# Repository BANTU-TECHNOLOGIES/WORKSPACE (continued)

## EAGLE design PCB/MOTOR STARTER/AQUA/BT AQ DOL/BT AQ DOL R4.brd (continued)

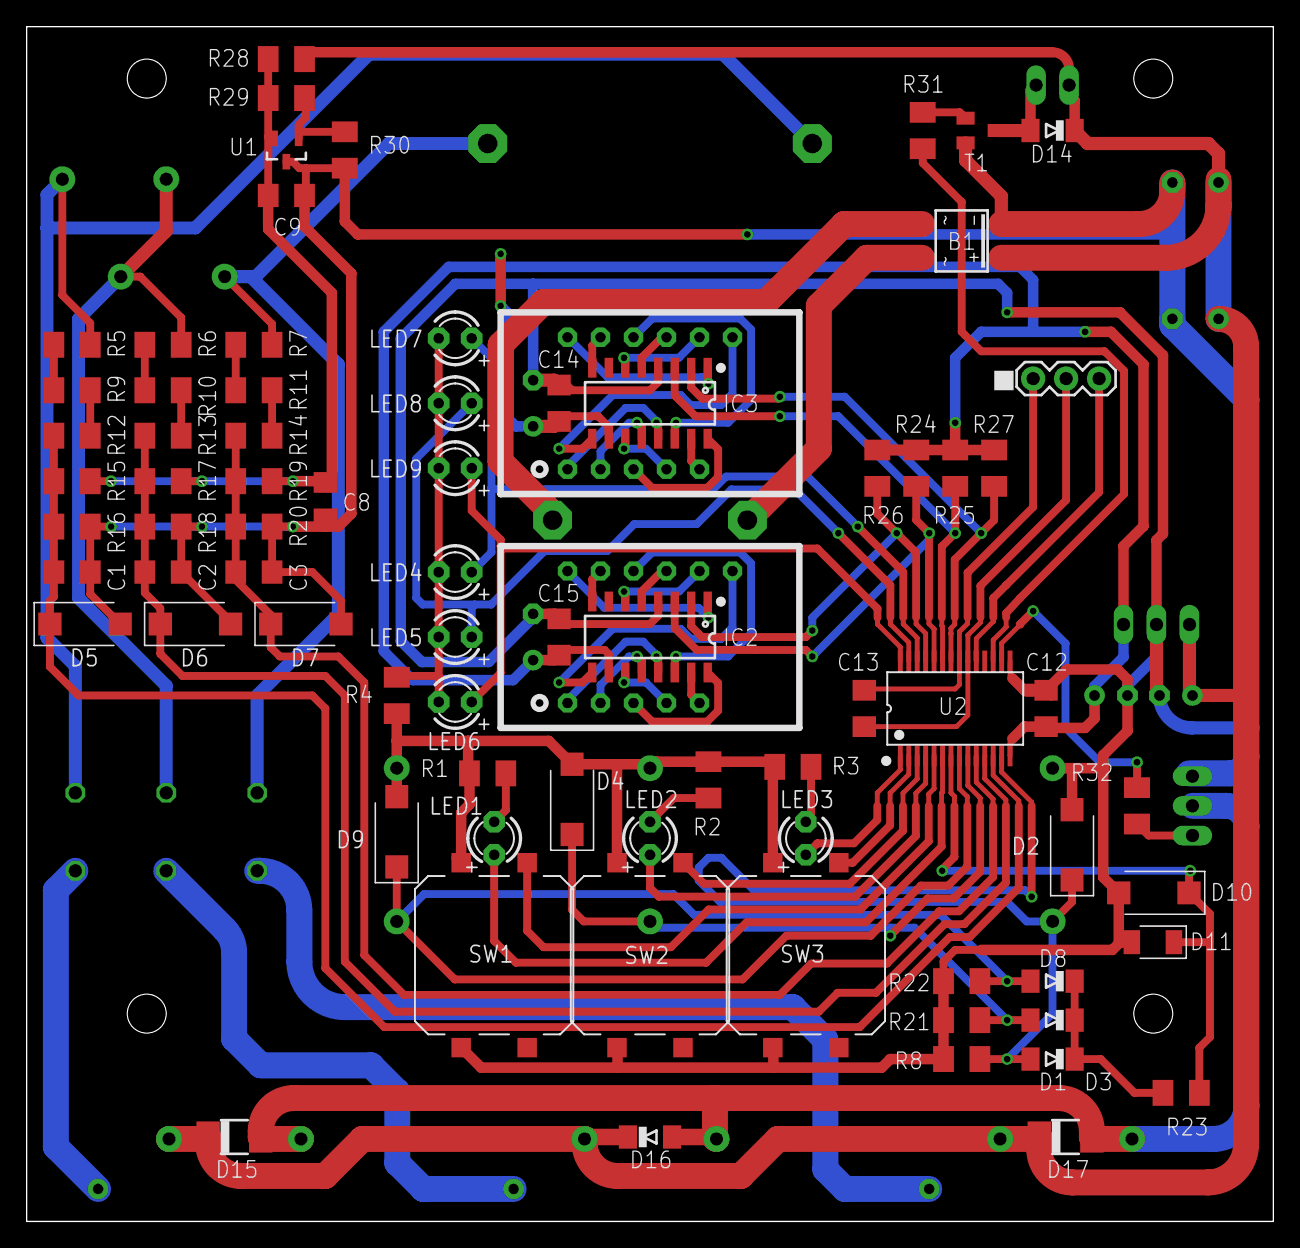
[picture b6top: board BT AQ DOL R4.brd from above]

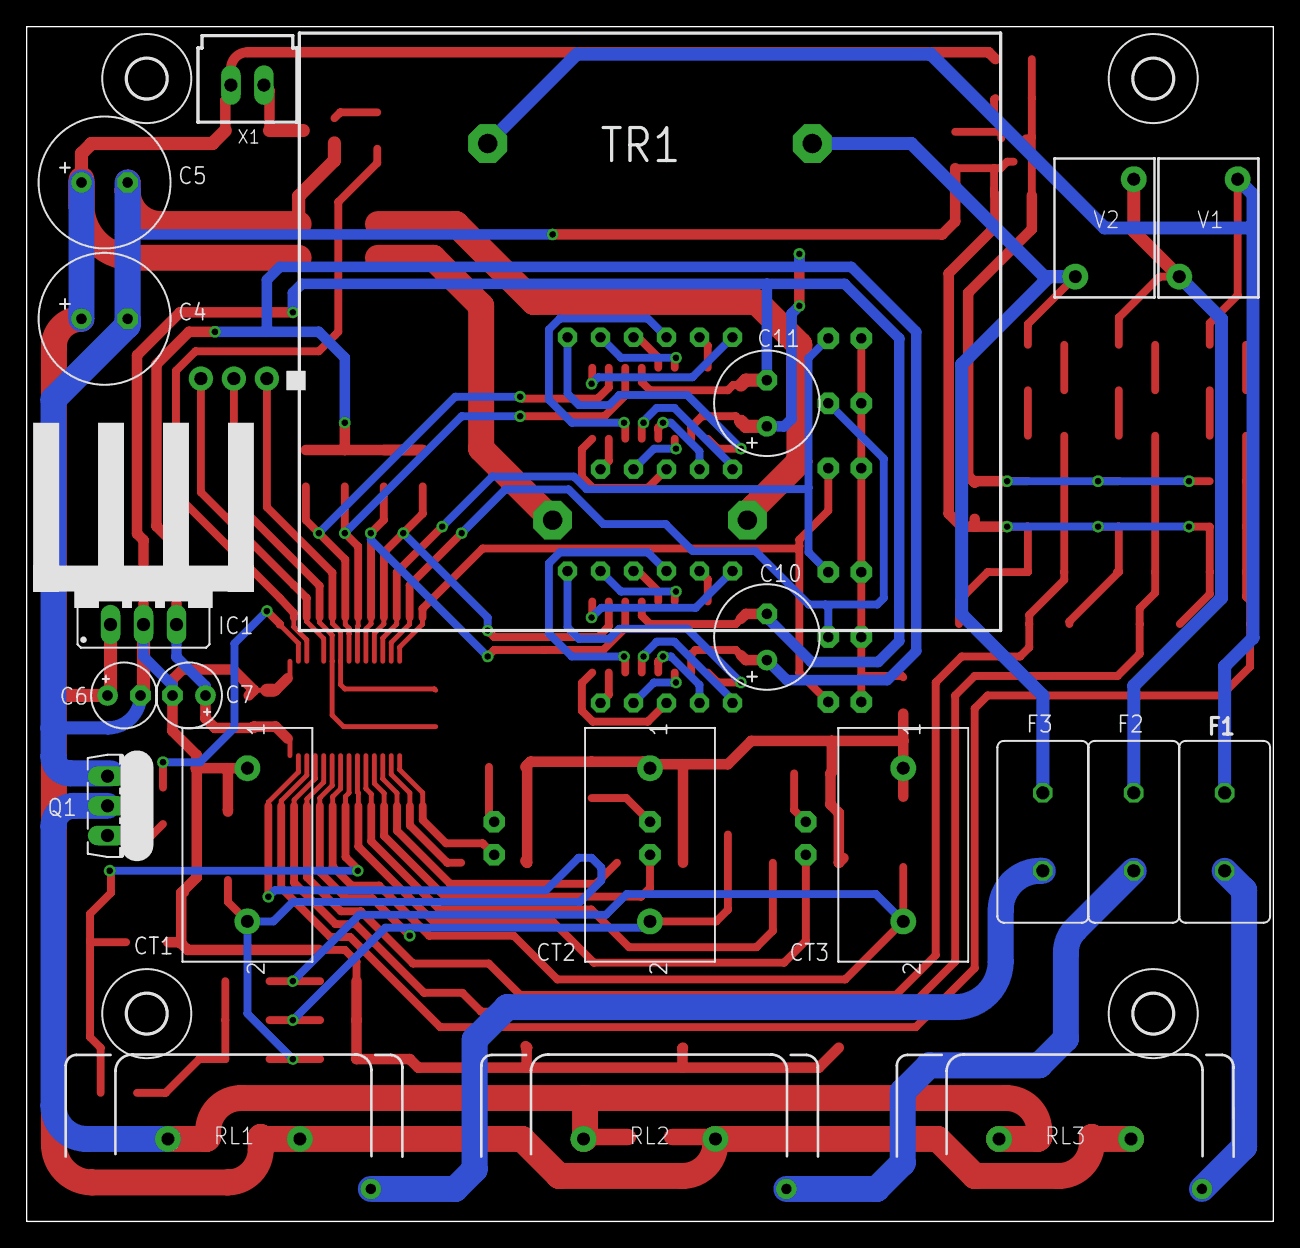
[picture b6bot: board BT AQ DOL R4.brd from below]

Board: 2 copper layers, 96.0 x 92.0 mm, 103 parts (26 on the bottom side), 70 nets.

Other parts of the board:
U$1, U$2, U$3, U$8: 3,0
U$4: TO220_17X13

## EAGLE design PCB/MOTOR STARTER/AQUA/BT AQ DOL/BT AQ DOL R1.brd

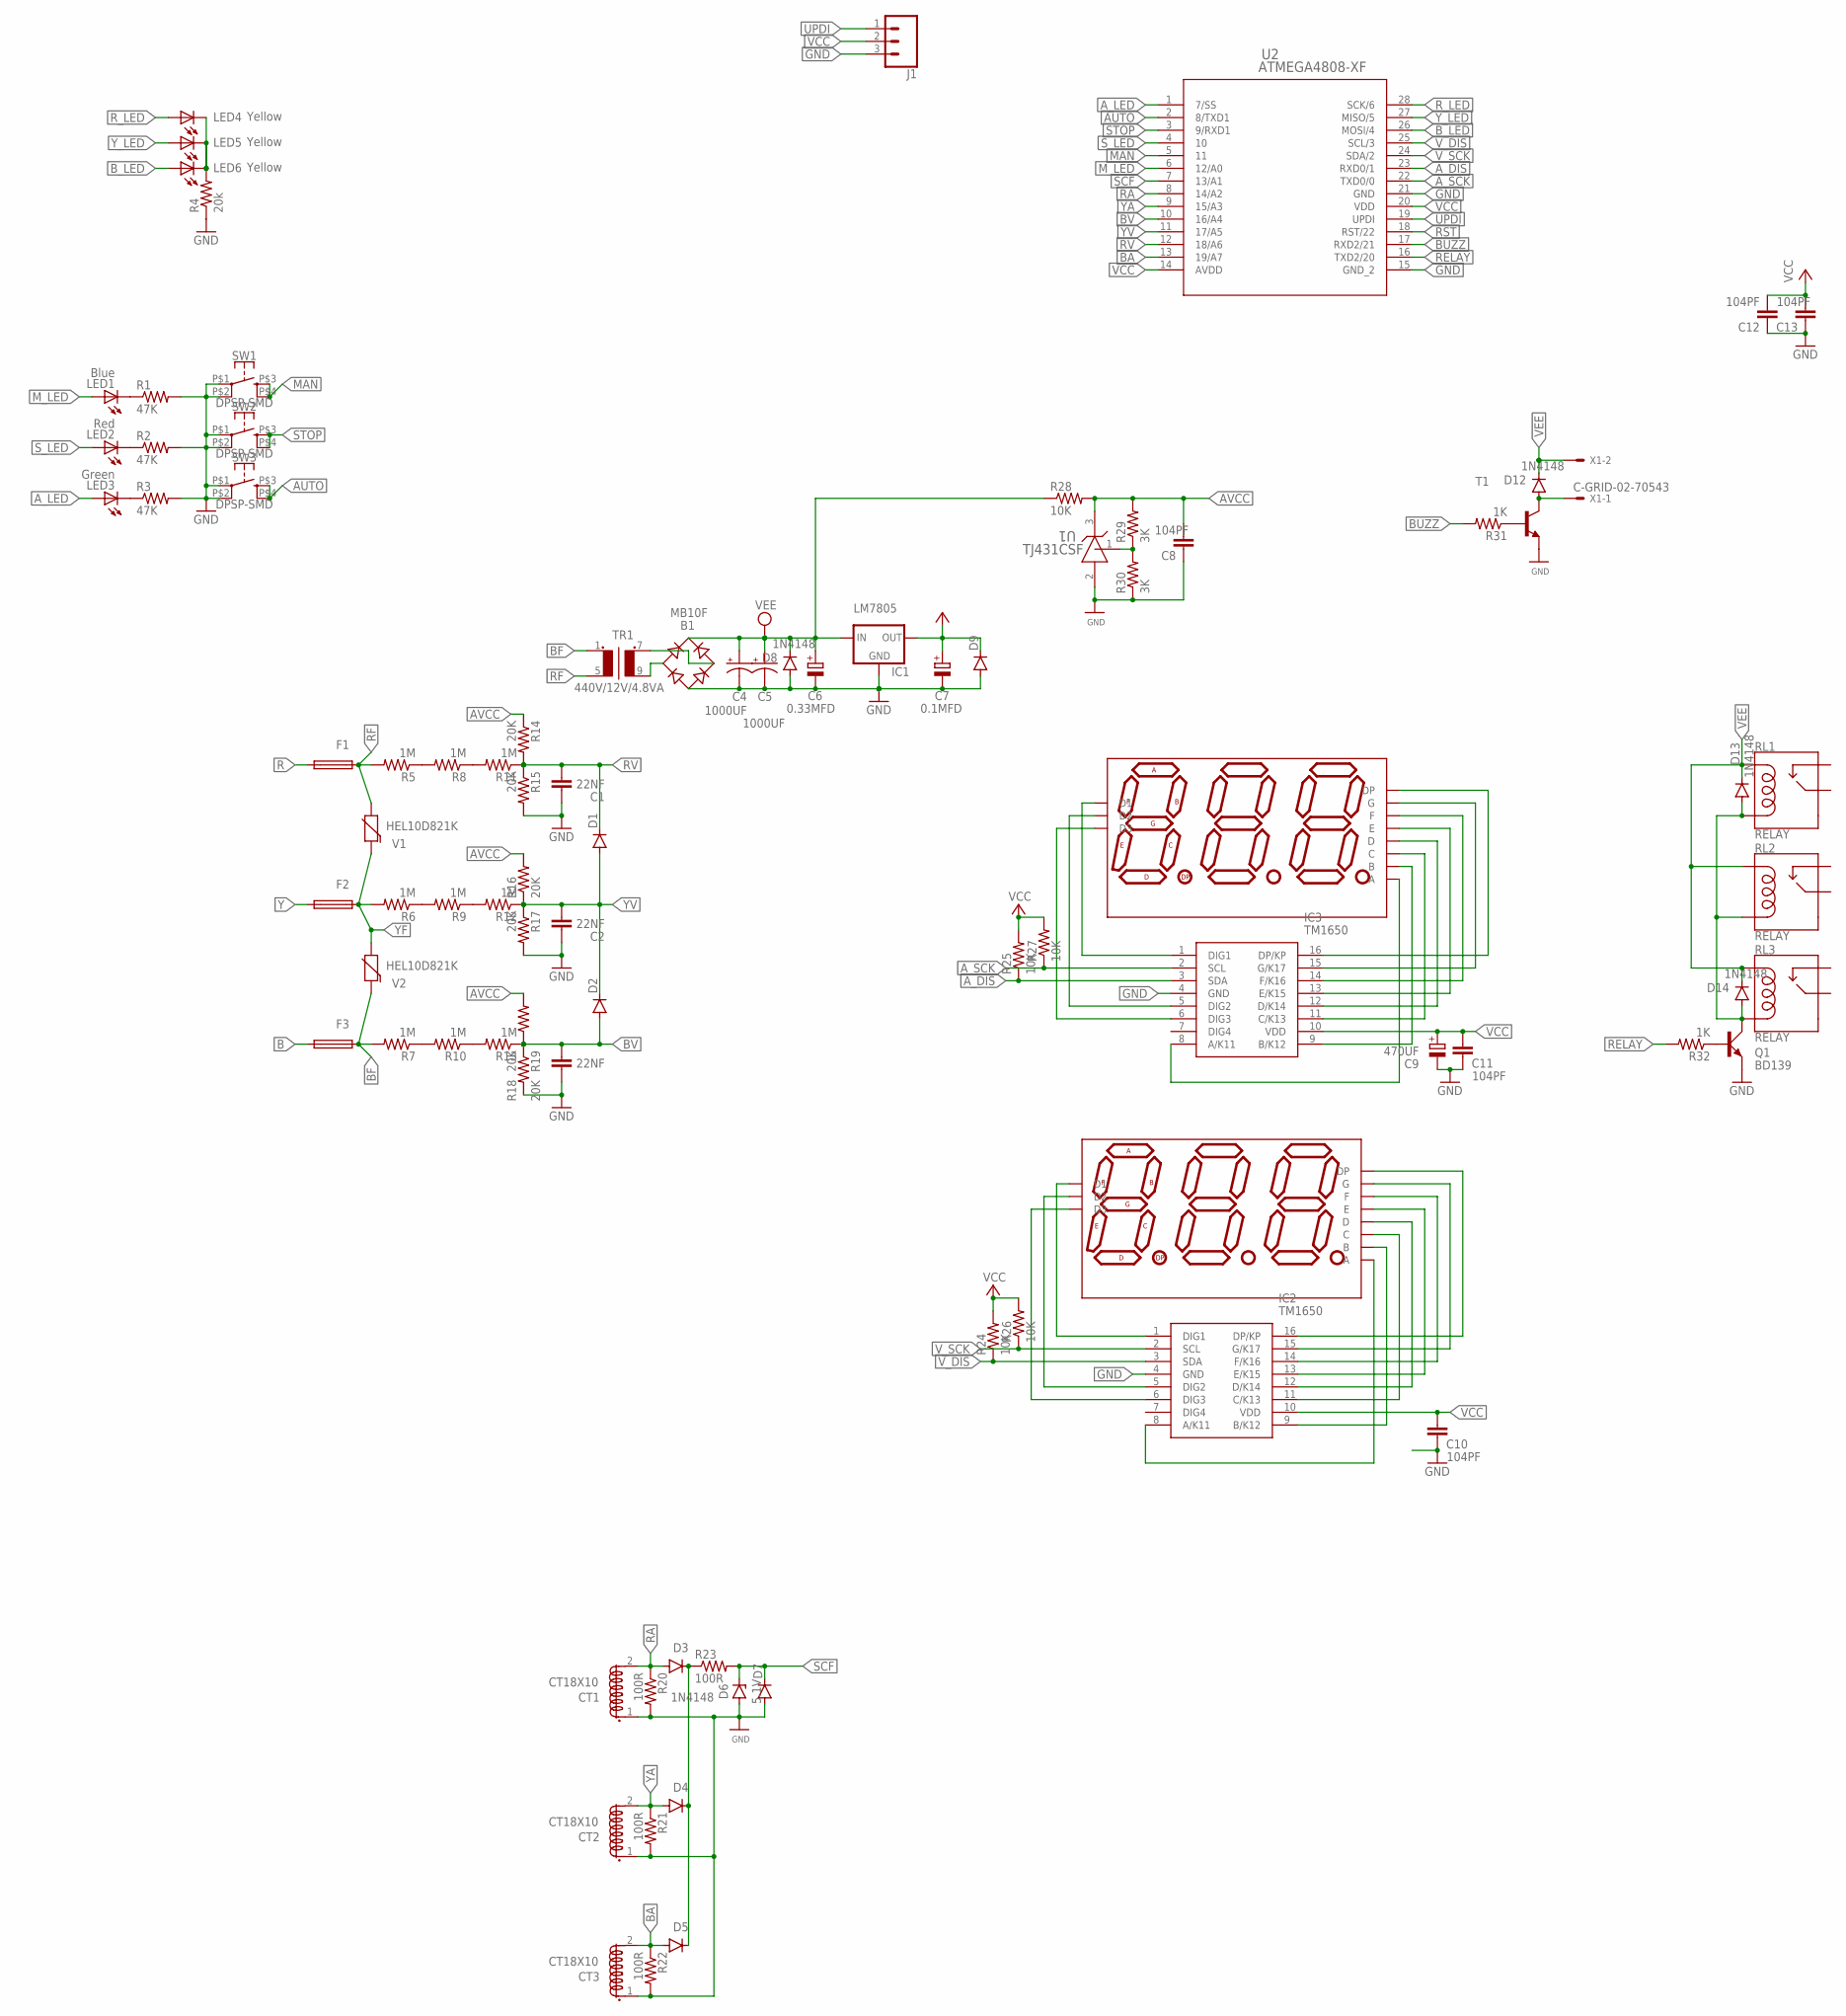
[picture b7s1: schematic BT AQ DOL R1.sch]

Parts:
B1: MB10F; SOIC-4
C1, C2, C3: 22NF; C1206
C4, C5: 1000UF; E3,5-10
C6: 0.33MFD; E2,5-5
C7: 0.1MFD; E2,5-5
C8, C10, C11, C12, C13: 104PF; C1206
C9: 470UF; E3,5-8
CT1, CT2, CT3: CT18X10; ZMCT103C
D1, D2, D7, D9: DIODE-DO214AA; DO214AA
D3, D4, D5, D8, D12, D14: 1N4148; MINIMELF
D6: 5.1V; DIOMELF3516
D10, D11: SUNR036CC3D; 7S3D036_DIP
D13: 1N4148; DO-214AC
F1, F2, F3: TRF600-150; TRF600-150-SMD
IC1: LM7805; 78XXS
IC2, IC3: TM1650; SOIC127P604X185-16N
J1: CONN_03; 1X03
LED1: Blue; LED3MM
LED2: Red; LED3MM
LED3: Green; LED3MM
LED4, LED5, LED6: Yellow; LED3MM
Q1: BD139; TO126AV
R1, R2, R3: 47K; M1206
R4: 20k; M1206
R5, R6, R7, R8, R9, R10, R11, R12, R13: 1M; M1206
R14, R15, R16, R17, R18, R19: 20K; M1206
R20, R21, R22, R23: 100R; M1206
R24, R25, R26, R27, R28: 10K; M1206
R29, R30: 3K; M1206
R31, R32: 1K; M1206
RL1, RL2, RL3: RELAY; DT81_RECTANGULAR
SW1, SW2, SW3: DPSP-SMD; B3F-40XX-ROUND-SMD
T1: MMUN2213LT1-NPN-SC59-BEC; SC59-BEC
TR1: 440V/12V/4.8VA; 440V12V6VA
U1: TJ431CSF; SOT-23
U2: ATMEGA4808-XF; SSOP28_SS_MCH
V1, V2: HEL10D821K; 10MM
X1: C-GRID-02-70543; 70543-02

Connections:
AUTO: SW3.P$3 (3), SW3.P$4 (4), U2.2 (8/TXD1)
AVCC: C8.2, R14.1, R16.2, R18.2, R28.2, R29.2, U1.3 (CATHODE)
A_DIS: IC3.3 (SDA), R25.1, U2.23 (RXD0/1)
A_LED: LED3.A, U2.1 (7/SS)
A_SCK: IC3.2 (SCL), R27.1, U2.22 (TXD0/0)
B: F3.1
BA: CT3.2 (S1.2), D5.A, R22.1, U2.13 (19/A7)
BF: F3.2, R7.2, TR1.1, V2.1
BUZZ: R31.2, U2.17 (RXD2/21)
BV: C3.2, D2.A, R13.1, R18.1, R19.1, U2.10 (16/A4)
B_LED: LED6.A, U2.26 (MOSI/4)
GND: B1.-, C1.1, C2.1, C3.1, C4.-, C5.-, C6.-, C7.-, C8.1, C9.-, C10.1, C11.1, C12.1, C13.1, CT1.1 (S1.1), CT2.1 (S1.1), CT3.1 (S1.1), D6.2 (A), D7.A, D8.A, D9.A, IC1.GND, IC2.4 (GND), IC3.4 (GND), J1.3, Q1.E, R1.2, R2.2, R3.2, R4.1, R15.2, R17.2, R19.2, R20.2, R21.2, R22.2, R30.1, SW1.P$1 (1), SW1.P$2 (2), SW2.P$1 (1), SW2.P$2 (2), SW3.P$1 (1), SW3.P$2 (2), T1.E, U1.2 (ANODE), U2.15 (GND_2), U2.21 (GND)
MAN: SW1.P$3 (3), SW1.P$4 (4), U2.5 (11)
M_LED: LED1.A, U2.6 (12/A0)
unnamed: B1.~2 (AC2), TR1.7 (S1)
unnamed: B1.~1 (AC1), TR1.9 (S2)
unnamed: D12.A, T1.C, X1.1
unnamed: R31.1, T1.B
unnamed: LED3.K (C), R3.1
unnamed: LED2.K (C), R2.1
unnamed: LED1.K (C), R1.1
unnamed: R29.1, R30.2, U1.1 (REF)
unnamed: R5.1, R8.2
unnamed: R8.1, R11.2
unnamed: R6.1, R9.2
unnamed: R7.1, R10.2
unnamed: R9.1, R12.2
unnamed: Q1.B, R32.1
unnamed: R10.1, R13.2
unnamed: D11.11 (A), IC3.8 (A/K11)
unnamed: D11.7 (B), IC3.9 (B/K12)
unnamed: D11.4 (C), IC3.11 (C/K13)
unnamed: D11.2 (D), IC3.12 (D/K14)
unnamed: D11.1 (E), IC3.13 (E/K15)
unnamed: D11.10 (F), IC3.14 (F/K16)
unnamed: D11.5 (G), IC3.15 (G/K17)
unnamed: D11.3 (DP), IC3.16 (DP/KP)
unnamed: D11.12 (D1), IC3.1 (DIG1)
unnamed: D11.9 (D2), IC3.5 (DIG2)
unnamed: D11.8 (D3), IC3.6 (DIG3)
unnamed: D10.11 (A), IC2.8 (A/K11)
unnamed: D10.7 (B), IC2.9 (B/K12)
unnamed: D10.4 (C), IC2.11 (C/K13)
unnamed: D3.C, D4.C, D5.C, R23.1
unnamed: D10.2 (D), IC2.12 (D/K14)
unnamed: LED4.K (C), LED5.K (C), LED6.K (C), R4.2
unnamed: D10.1 (E), IC2.13 (E/K15)
unnamed: D10.10 (F), IC2.14 (F/K16)
unnamed: D10.5 (G), IC2.15 (G/K17)
unnamed: D10.3 (DP), IC2.16 (DP/KP)
unnamed: D10.12 (D1), IC2.1 (DIG1)
unnamed: D10.9 (D2), IC2.5 (DIG2)
unnamed: D10.8 (D3), IC2.6 (DIG3)
unnamed: D13.A, D14.A, Q1.C, RL1.2 (COIL2), RL1.2. (COIL2), RL2.2 (COIL2), RL2.2. (COIL2), RL3.2 (COIL2), RL3.2. (COIL2)
R: F1.1
RA: CT1.2 (S1.2), D3.A, R20.1, U2.8 (14/A2)
RELAY: R32.2, U2.16 (TXD2/20)
RF: F1.2, R5.2, TR1.5 (P2), V1.2
RST: U2.18 (RST/22)
RV: C1.2, D1.C, R11.1, R14.2, R15.1, U2.12 (18/A6)
R_LED: LED4.A, U2.28 (SCK/6)
SCF: D6.1 (C), D7.C, R23.2, U2.7 (13/A1)
STOP: SW2.P$3 (3), SW2.P$4 (4), U2.3 (9/RXD1)
S_LED: LED2.A, U2.4 (10)
UPDI: J1.1, U2.19 (UPDI)
VCC: C7.+, C9.+, C10.2, C11.2, C12.2, C13.2, D9.C, IC1.OUT, IC2.10 (VDD), IC3.10 (VDD), J1.2, R24.2, R25.2, R26.2, R27.2, U2.14 (AVDD), U2.20 (VDD)
VEE: B1.+, C4.+, C5.+, C6.+, D8.C, D12.C, D13.C, D14.C, IC1.IN, R28.1, RL1.1 (COIL1), RL1.1. (COIL1), RL2.1 (COIL1), RL2.1. (COIL1), RL3.1 (COIL1), RL3.1. (COIL1), X1.2
V_DIS: IC2.3 (SDA), R24.1, U2.25 (SCL/3)
V_SCK: IC2.2 (SCL), R26.1, U2.24 (SDA/2)
Y: F2.1
YA: CT2.2 (S1.2), D4.A, R21.1, U2.9 (15/A3)
YF: F2.2, R6.2, V1.1, V2.2
YV: C2.2, D1.A, D2.C, R12.1, R16.1, R17.1, U2.11 (17/A5)
Y_LED: LED5.A, U2.27 (MISO/5)

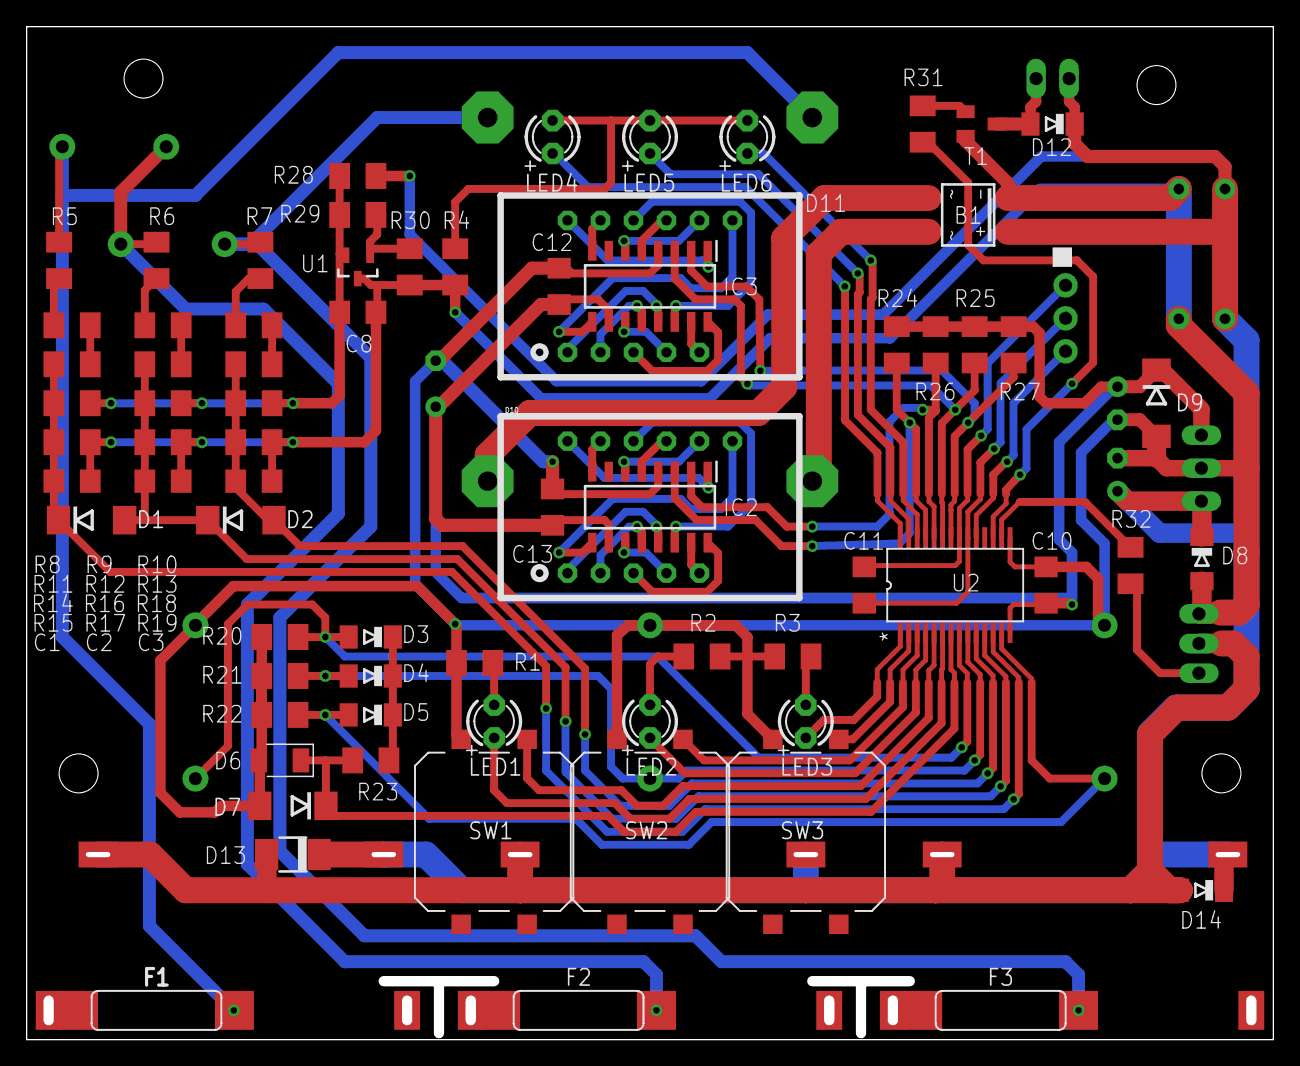
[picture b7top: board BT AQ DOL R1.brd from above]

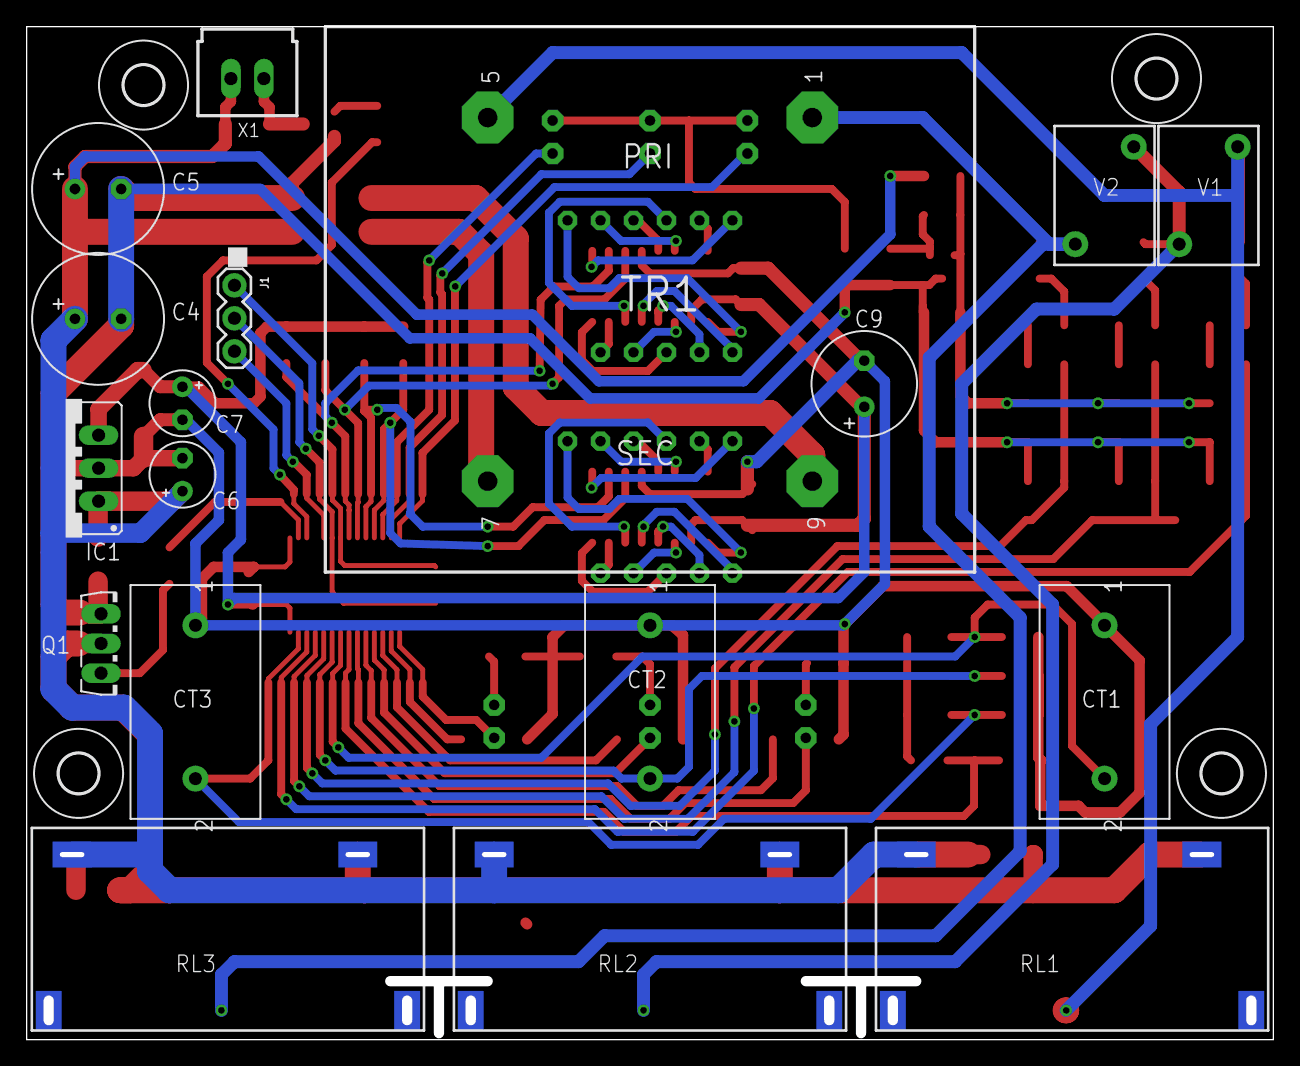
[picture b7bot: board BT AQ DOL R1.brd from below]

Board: 2 copper layers, 96.0 x 78.0 mm, 94 parts (22 on the bottom side), 70 nets.

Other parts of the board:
U$1, U$2, U$3, U$8: 3,0

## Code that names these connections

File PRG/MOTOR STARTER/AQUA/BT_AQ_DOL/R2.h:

#ifndef _R2_H
#define _R2_H

String HWV = "H02";

TM1650 module1(1, 0, 3);    // data, clock, digits
TM1650 module2(3, 2, 3);    // data, clock, digits
TM16xxDisplay V_DISP(&module1, 3);    // TM16xx object, 8 digits
TM16xxDisplay A_DISP(&module2, 3);    // TM16xx object, 8 digits

#define B_LED 4
#define Y_LED 5
#define R_LED 6
#define LED_AUTO 7
#define AUTO_PB_PIN 8
#define STOP_PB_PIN 9
#define LED_STOP 10
#define MAN_PB_PIN 11
#define LED_MAN 12
#define RELAY 20
#define BUZZER 21
#define SCF_PIN 13
//  AmplitudePins[6] =   RA  RV  YA  YV  BA  BV
int AMPLITUDE_PIN[8] = { A2, A6, A3, A5, A7, A4, A6, A6 }; 

bool LED = LOW;
int SET_AGAIN_MIN = 600;
int SET_AGAIN_MAX = 800;
int SET_OC_MAX = 65;
int SET_HP_MAX = 3;
double CT_MAX_RMS_AMP = 16.0;

#endif 

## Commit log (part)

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2026-06-18 INITIAL SETUP
